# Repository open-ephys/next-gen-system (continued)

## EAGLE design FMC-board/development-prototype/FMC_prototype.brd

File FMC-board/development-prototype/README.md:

# FMC daughter board development prototype

FMC LPC pinout diagram at:
https://docs.google.com/spreadsheets/d/1bgnBP1xqPFtFIQYF-BCybK1KkekfmRYwm2GDAU4D9lo/edit?usp=sharing

Features:

1x FMC connector (use LPC side, seems marginally easier to solder and we dont need the high pin count right now)
https://forums.xilinx.com/t5/Xilinx-Boards-and-Kits/FMC-Where-to-buy/td-p/44218
https://www.samtec.com/standards/fmc#asicdevelopment

~2-4 Omnmetics connectors for intan SPI cables to headstages
Maybe implement 1-2 SPI port with proper electrical decoupling (based on existing headstage decoupling board, but omit DC-DC transformer), but add at least an equal number of non-decoupled ones just in case there's an iissue with the circuit.

Testpoints & SMA connectors for probing things

At least ~4 (protected?) SMA or BNC in- and outputs to/from the FPGA for closed-loop tests.
Do we want to add level shifters or anything that can drive more current than the bare fpga pins?

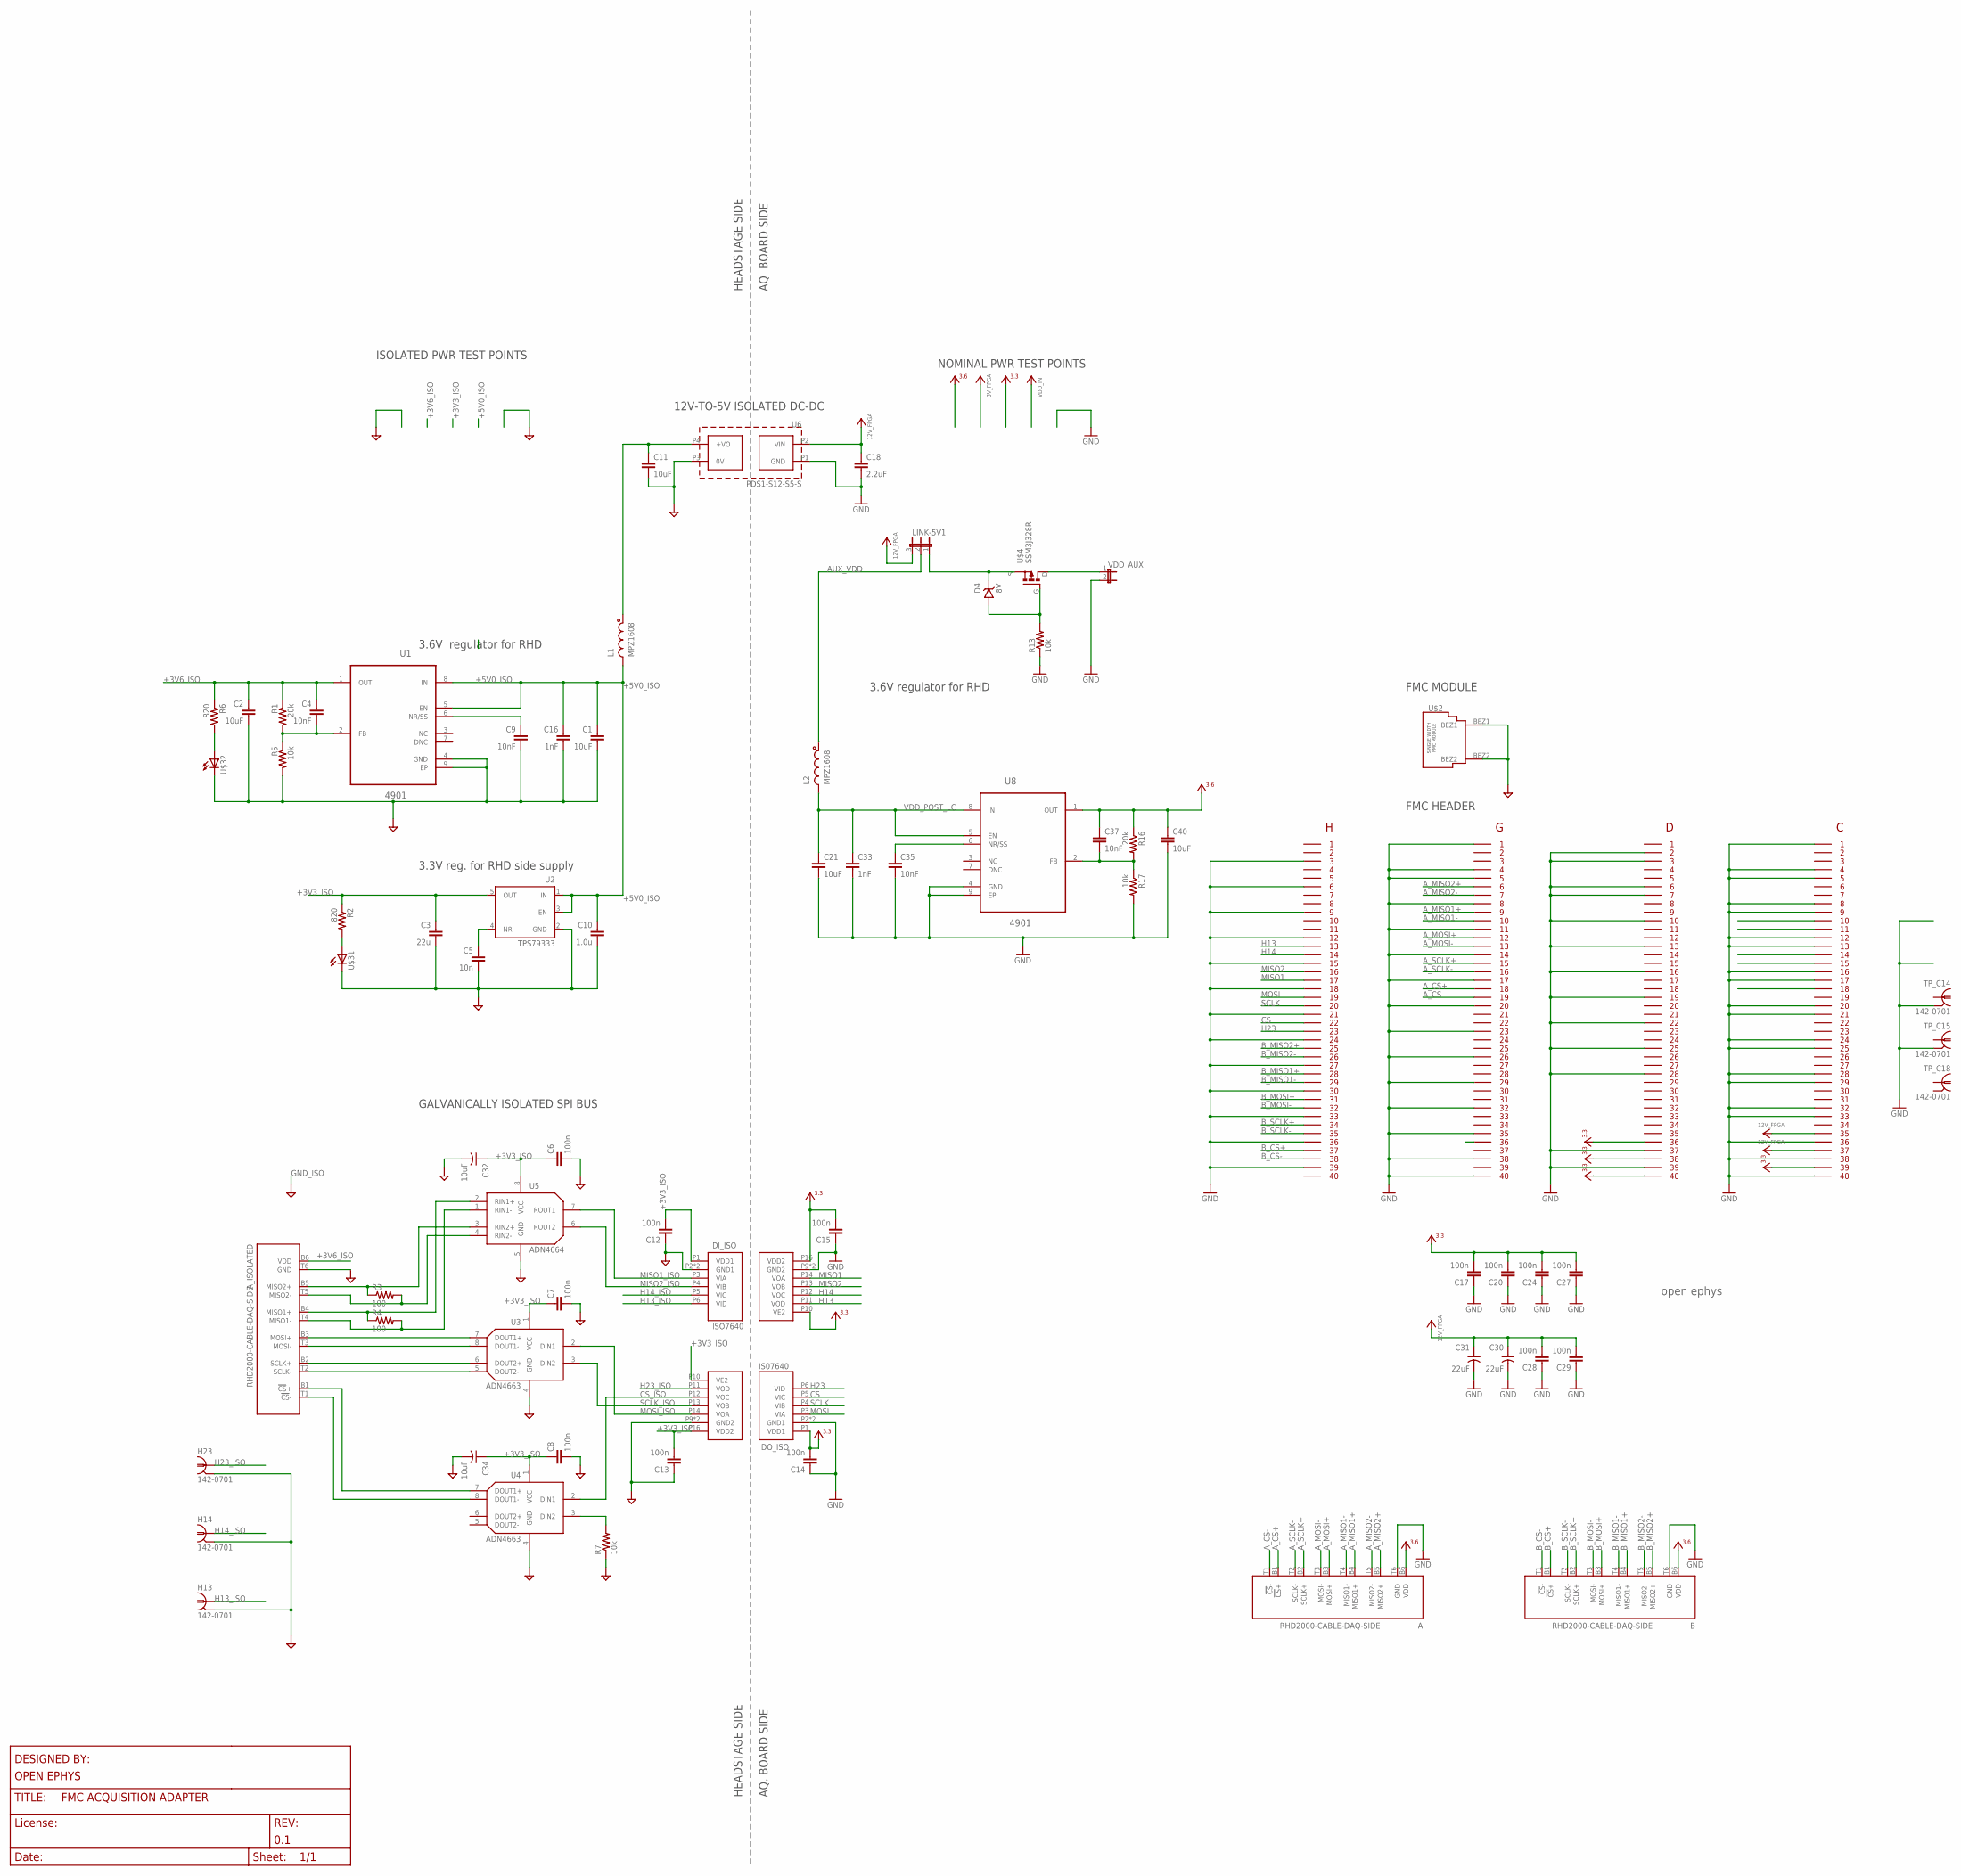
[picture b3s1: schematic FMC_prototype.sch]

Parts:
A: RHD2000-CABLE-DAQ-SIDE; OMNETICS_PZN-12-AA
A_ISOLATED: RHD2000-CABLE-DAQ-SIDE; OMNETICS_PZN-12-AA
B: RHD2000-CABLE-DAQ-SIDE; OMNETICS_PZN-12-AA
C1, C2, C11, C21, C40: 10uF; 1206
C3: 22u; 1206
C4, C9, C35, C37: 10nF; 0603
C5: 10n; 0603
C6, C7, C8, C12, C13, C14, C15, C17, C20, C24, C27, C28, C29: 100n; 0603
C10: 1.0u; 0805
C16, C33: 1nF; 0603
C18: 2.2uF; 1206
C30, C31: 22uF; 1210-POL
C32, C34: 10uF; 1206-POL
D4: 8V; SOD-323
DI_ISO: ISO7640; SOIC_WIDE_16
DO_ISO: IS07640; SOIC_WIDE_16
FMC: FMC_LPC_160_PIN; FMC_LPC_MALE_WITH_SP601_BSILK
H13, H14, H23: 142-0701; SMA_JACK_CONREVSMA002-G
L1, L2: MPZ1608; 0603
LINK-5V1: JP2E; JP2
R1, R16: 20k; 0603
R2, R6: 820; 0603
R3, R4: 100; 0603
R5, R7, R13, R17: 10k; 0603
TP_C14, TP_C15, TP_C18: 142-0701; SMA_JACK_142-0701-201
U1, U8: 4901; SOP65P490X110-9N
U2: TPS79333; SOT-23-5
U3, U4: ADN4663; SOIC127P500X400-8N
U5: ADN4664; SOIC127P500X400-8N
U6: PDS1-S12-S5-S; PDS1
U$1: OPEN_EPHYS_LOGO
U$2: FMC_SINGLE_WIDTH_MODULE
U$3: LED_2X_VERTICAL; 569-011X-X00_LED_ARRAY
U$4: SSM3J328R; SOT23-GSD
VDD_AUX: JP2E_THRU-HOLE; JP2

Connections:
12V_FPGA: C18.1, C28.2, C29.2, C30.+, C31.+, FMC.P$155, FMC.P$157, LINK-5V1.3, U6.P2 (VIN)
+3V3: C14.2, C15.2, C17.2, C20.2, C24.2, C27.2, DI_ISO.P10 (VE2), DI_ISO.P16 (VDD2), DO_ISO.P1 (VDD1), FMC.P$116, FMC.P$118, FMC.P$120, FMC.P$159
+3V3_ISO: C3.1, C6.1, C7.1, C8.1, C12.2, C13.2, C32.+, C34.+, DI_ISO.P1 (VDD1), DO_ISO.P10 (VE2), DO_ISO.P16 (VDD2), R2.1, U2.5 (OUT), U3.1 (VCC), U4.1 (VCC), U5.8 (VCC)
+3V6: A.B6 (VDD), B.B6 (VDD), C37.1, C40.1, R16.1, U8.1 (OUT)
+3V6_ISO: A_ISOLATED.B6 (VDD), C2.1, C4.1, R1.1, R6.1, U1.1 (OUT)
+5V0_ISO: C1.1, C10.1, C16.1, L1.2, U1.5 (EN), U1.8 (IN), U2.1 (IN), U2.3 (EN)
+5V0_ISO-PRE: C11.1, L1.1, U6.P4 (+VO)
AGND1: C37.2, R16.2, R17.1, U8.2 (FB)
AGND2: C4.2, R1.2, R5.1, U1.2 (FB)
AUX_VDD: L2.1, LINK-5V1.2
A_CS+: A.B1 (!CS!+), FMC.P$58
A_CS-: A.T1 (!CS!-), FMC.P$59
A_MISO1+: A.B4 (MISO1+), FMC.P$49
A_MISO1-: A.T4 (MISO1-), FMC.P$50
A_MISO2+: A.B5 (MISO2+), FMC.P$46
A_MISO2-: A.T5 (MISO2-), FMC.P$47
A_MOSI+: A.B3 (MOSI+), FMC.P$52
A_MOSI-: A.T3 (MOSI-), FMC.P$53
A_SCLK+: A.B2 (SCLK+), FMC.P$55
A_SCLK-: A.T2 (SCLK-), FMC.P$56
B_CS+: B.B1 (!CS!+), FMC.P$37
B_CS-: B.T1 (!CS!-), FMC.P$38
B_MISO1+: B.B4 (MISO1+), FMC.P$28
B_MISO1-: B.T4 (MISO1-), FMC.P$29
B_MISO2+: B.B5 (MISO2+), FMC.P$25
B_MISO2-: B.T5 (MISO2-), FMC.P$26
B_MOSI+: B.B3 (MOSI+), FMC.P$31
B_MOSI-: B.T3 (MOSI-), FMC.P$32
B_SCLK+: B.B2 (SCLK+), FMC.P$34
B_SCLK-: B.T2 (SCLK-), FMC.P$35
C10: FMC.P$130
C11: FMC.P$131
C14: FMC.P$134
C18: FMC.P$138
CS: DO_ISO.P5 (VIC), FMC.P$22
CS+_ISOLATED: A_ISOLATED.B1 (!CS!+), U4.7 (DOUT1+)
CS-_ISOLATED: A_ISOLATED.T1 (!CS!-), U4.8 (DOUT1-)
CS_ISO: DO_ISO.P12 (VOC), U4.2 (DIN1)
GND: A.T6 (GND), B.T6 (GND), C14.1, C15.1, C17.1, C18.2, C20.1, C21.2, C24.1, C27.1, C28.1, C29.1, C30.-, C31.-, C33.2, C35.2, C40.2, DI_ISO.P9 (GND2), DI_ISO.P15 (GND2), DO_ISO.P2 (GND1), DO_ISO.P8 (GND1), FMC.GNDA (GND), FMC.GNDB (GND), FMC.P$3, FMC.P$6, FMC.P$9, FMC.P$12, FMC.P$15, FMC.P$18, FMC.P$21, FMC.P$24, FMC.P$27, FMC.P$30, FMC.P$33, FMC.P$36, FMC.P$39, FMC.P$41, FMC.P$44, FMC.P$45, FMC.P$48, FMC.P$51, FMC.P$54, FMC.P$57, FMC.P$60, FMC.P$63, FMC.P$66, FMC.P$69, FMC.P$72, FMC.P$75, FMC.P$78, FMC.P$80, FMC.P$82, FMC.P$83, FMC.P$86, FMC.P$87, FMC.P$90, FMC.P$93, FMC.P$96, FMC.P$99, FMC.P$102, FMC.P$105, FMC.P$108, FMC.P$117, FMC.P$119, FMC.P$121, FMC.P$124, FMC.P$125, FMC.P$128, FMC.P$129, FMC.P$132, FMC.P$133, FMC.P$136, FMC.P$137, FMC.P$140, FMC.P$141, FMC.P$144, FMC.P$145, FMC.P$148, FMC.P$149, FMC.P$152, FMC.P$153, FMC.P$156, FMC.P$158, FMC.P$160, R13.1, R17.2, TP_C14.GND$1 (2), TP_C14.GND$2 (2), TP_C14.GND$3 (2), TP_C14.GND$4 (2), TP_C15.GND$1 (2), TP_C15.GND$2 (2), TP_C15.GND$3 (2), TP_C15.GND$4 (2), U6.P1 (GND), U8.4 (GND), U8.9 (EP), VDD_AUX.2
GND_ISO: A_ISOLATED.T6 (GND), C1.2, C2.2, C3.2, C5.2, C6.2, C7.2, C8.2, C9.2, C10.2, C11.2, C12.1, C13.1, C16.2, C32.-, C34.-, DI_ISO.P2 (GND1), DI_ISO.P8 (GND1), DO_ISO.P9 (GND2), DO_ISO.P15 (GND2), H13.GND$1 (2), H13.GND$2 (2), H13.GND$3 (2), H13.GND$4 (2), H14.GND$1 (2), H14.GND$2 (2), H14.GND$3 (2), H14.GND$4 (2), H23.GND$1 (2), H23.GND$2 (2), H23.GND$3 (2), H23.GND$4 (2), R5.2, R7.1, U1.4 (GND), U1.9 (EP), U2.2 (GND), U3.4 (GND), U4.4 (GND), U5.5 (GND), U6.P3 (0V), U$2.BEZ1, U$2.BEZ2, U$3.C1 (C), U$3.C2 (C)
H13: DI_ISO.P11 (VOD), FMC.P$13
H13_ISO: DI_ISO.P6 (VID), H13.CLK (1)
H14: DI_ISO.P12 (VOC), FMC.P$14
H14_ISO: DI_ISO.P5 (VIC), H14.CLK (1)
H23: DO_ISO.P6 (VID), FMC.P$23
H23_ISO: DO_ISO.P11 (VOD), H23.CLK (1)
MISO1: DI_ISO.P14 (VOA), FMC.P$17
MISO1+_ISOLATED: A_ISOLATED.B4 (MISO1+), R4.1, U5.2 (RIN1+)
MISO1-_ISOLATED: A_ISOLATED.T4 (MISO1-), R4.2, U5.1 (RIN1-)
MISO1_ISO: DI_ISO.P3 (VIA), U5.7 (ROUT1)
MISO2: DI_ISO.P13 (VOB), FMC.P$16
MISO2+_ISOLATED: A_ISOLATED.B5 (MISO2+), R3.1, U5.3 (RIN2+)
MISO2-_ISOLATED: A_ISOLATED.T5 (MISO2-), R3.2, U5.4 (RIN2-)
MISO2_ISO: DI_ISO.P4 (VIB), U5.6 (ROUT2)
MOSI: DO_ISO.P3 (VIA), FMC.P$19
MOSI_ISO: DO_ISO.P14 (VOA), U3.2 (DIN1)
unnamed: C35.1, U8.6 (NR/SS)
unnamed: D4.C, LINK-5V1.1, U$4.S
unnamed: C9.1, U1.6 (NR/SS)
unnamed: R7.2, U4.3 (DIN2)
unnamed: D4.A, R13.2, U$4.G
unnamed: U$4.D, VDD_AUX.1
unnamed: R6.2, U$3.A2 (A)
unnamed: R2.2, U$3.A1 (A)
unnamed: A_ISOLATED.B3 (MOSI+), U3.7 (DOUT1+)
unnamed: A_ISOLATED.T3 (MOSI-), U3.8 (DOUT1-)
unnamed: A_ISOLATED.B2 (SCLK+), U3.6 (DOUT2+)
unnamed: A_ISOLATED.T2 (SCLK-), U3.5 (DOUT2-)
unnamed: C5.1, U2.4 (NR)
SCLK: DO_ISO.P4 (VIB), FMC.P$20
SCLK_ISO: DO_ISO.P13 (VOB), U3.3 (DIN2)
TP7: FMC.P$135
VDD_POST_LC: C21.1, C33.1, L2.2, U8.5 (EN), U8.8 (IN)

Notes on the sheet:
HEADSTAGE SIDE
AQ. BOARD SIDE
3.3V reg. for RHD side supply
3.6V regulator for RHD
12V-TO-5V ISOLATED DC-DC
ISOLATED PWR TEST POINTS
NOMINAL PWR TEST POINTS
3.6V regulator for RHD
GALVANICALLY ISOLATED SPI BUS
FMC HEADER
FMC MODULE

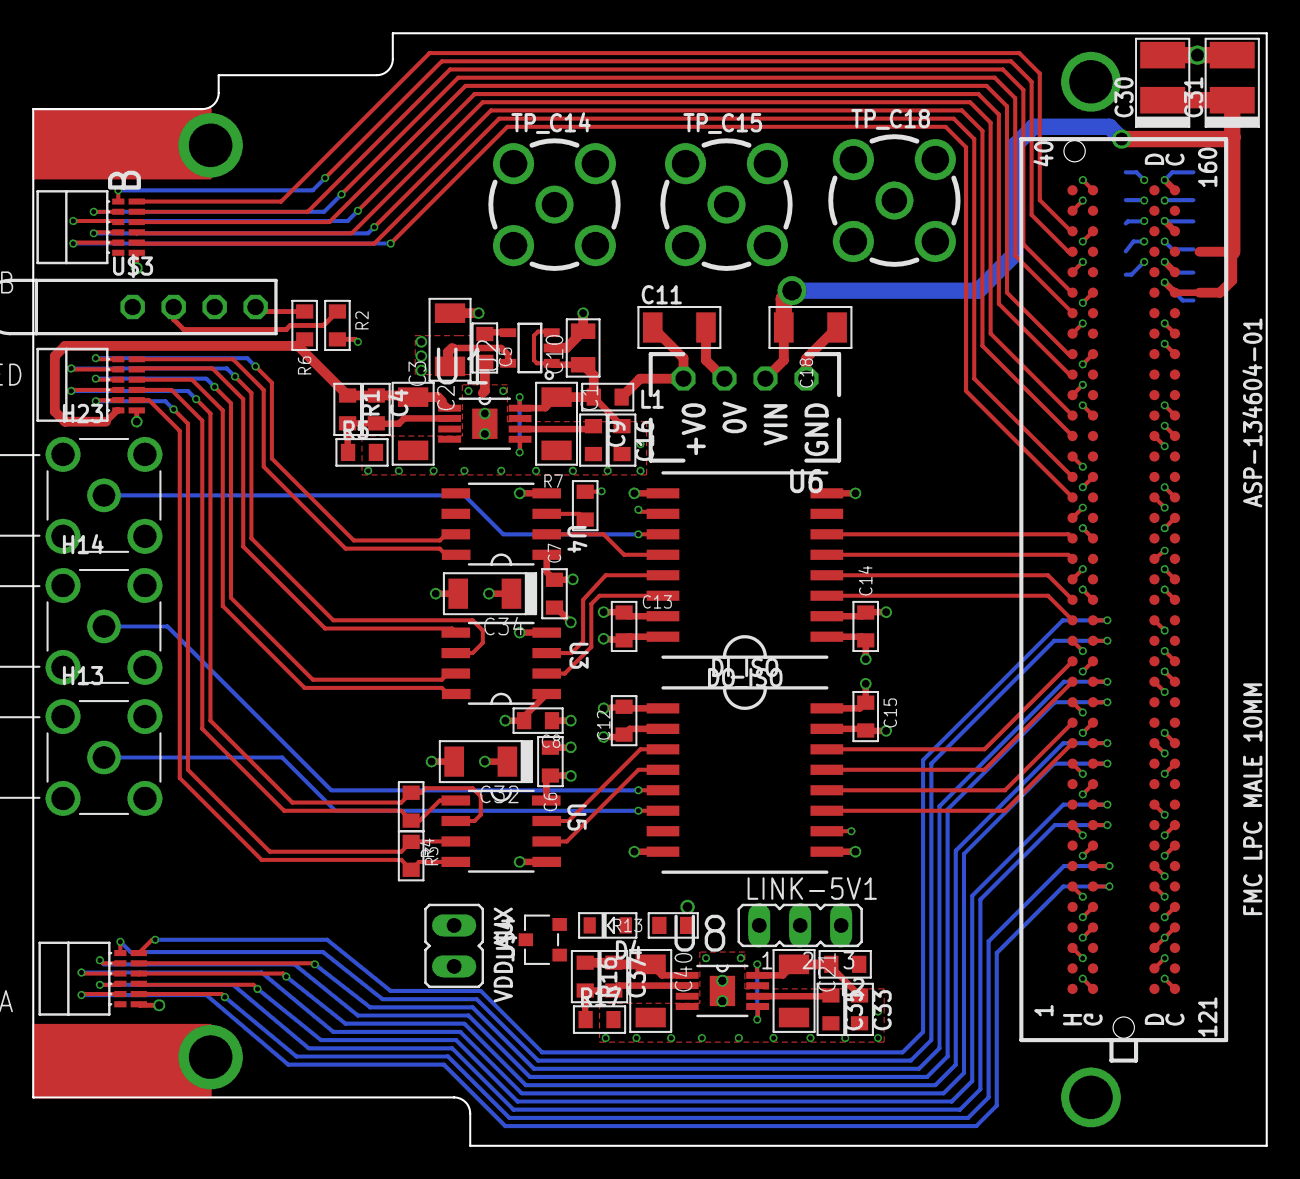
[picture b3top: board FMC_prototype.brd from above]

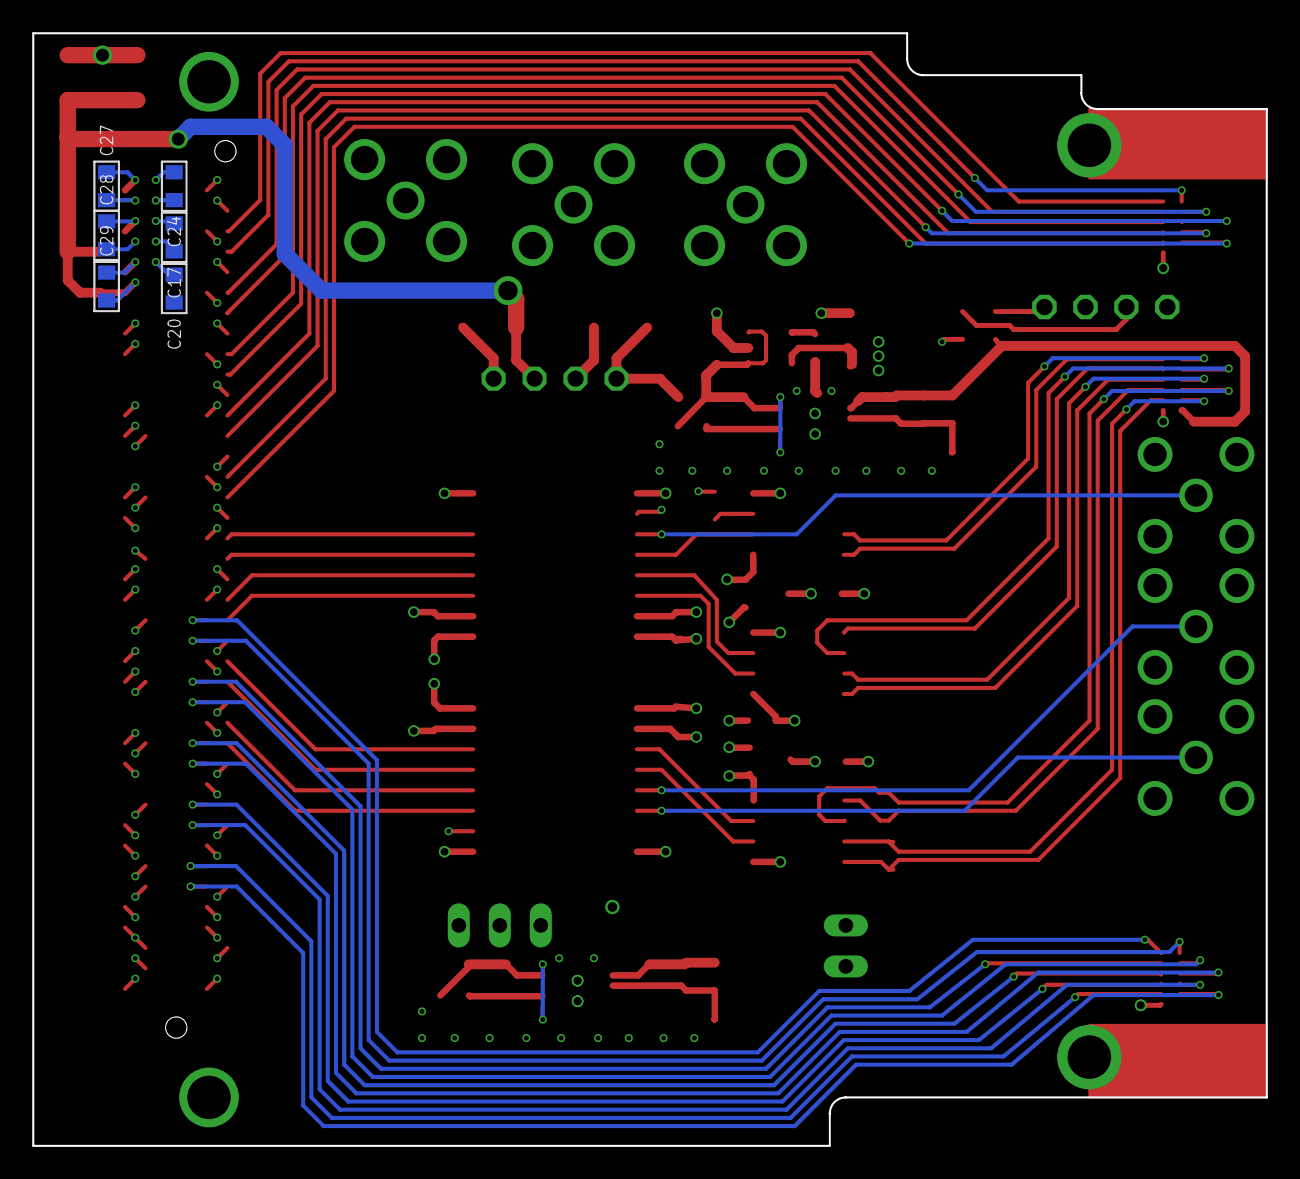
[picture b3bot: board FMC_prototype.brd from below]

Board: 4 copper layers, 76.5 x 69.0 mm, 71 parts (7 on the bottom side), 68 nets.

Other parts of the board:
U$16: INTAN_LOGO

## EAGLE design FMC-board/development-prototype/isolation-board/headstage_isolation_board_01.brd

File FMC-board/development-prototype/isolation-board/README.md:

# headstage-isolation-board
isolation board for RHD headstge, electrically decouples headstage from aq. board.
This could be useful for mitigating recording noise in some scenarious, or simplify proper grounding practive, especially if multiple recording rigs share the same acquisition board. Eventually, this device could be used to provide safety for human EEG or intracortical applications, but this would require extensive testing and approval procedures.

*This device has not been tested and is not considered safe for any use case. Only use this if you are approved to do so independently.*

# operating principle
This isolation board translates the LVDS signals to a single ended CMOS signal, isolates this signal and translates it back to LVDS. Power isolation is accomplished through a separate 5V isolation transformer.

Based on Analog Devices ADUM3440 isolators 9 http://www.analog.com/media/en/technical-documentation/data-sheets/ADuM3440_3441_3442.pdf )
UL recognition: 2500 V rms for 1 minute per UL 1577,  CSA Component Acceptance Notice #5A, VDE certificate of conformity, DIN V VDE V 0884-10 (VDE V 0884-10):2006-12 
V_IORM = 560 V peak

LVDS<-> CMOS trsnalation is done via on Analog Devices ADN4664 Dual, 3 V, CMOS, LVDS Differential Line Receivers ( http://www.analog.com/media/en/technical-documentation/data-sheets/ADN4664.pdf ) and ADN4663 Dual, 3 V, CMOS, LVDS High Speed Differential Drivers ( http://www.analog.com/media/en/technical-documentation/data-sheets/ADN4663.pdf )

Power isolation is done with a Murata NMV0505 3kVDC Isolated 5V DC/DC Converters ( http://power.murata.com/data/power/ncl/kdc_nmv.pdf )

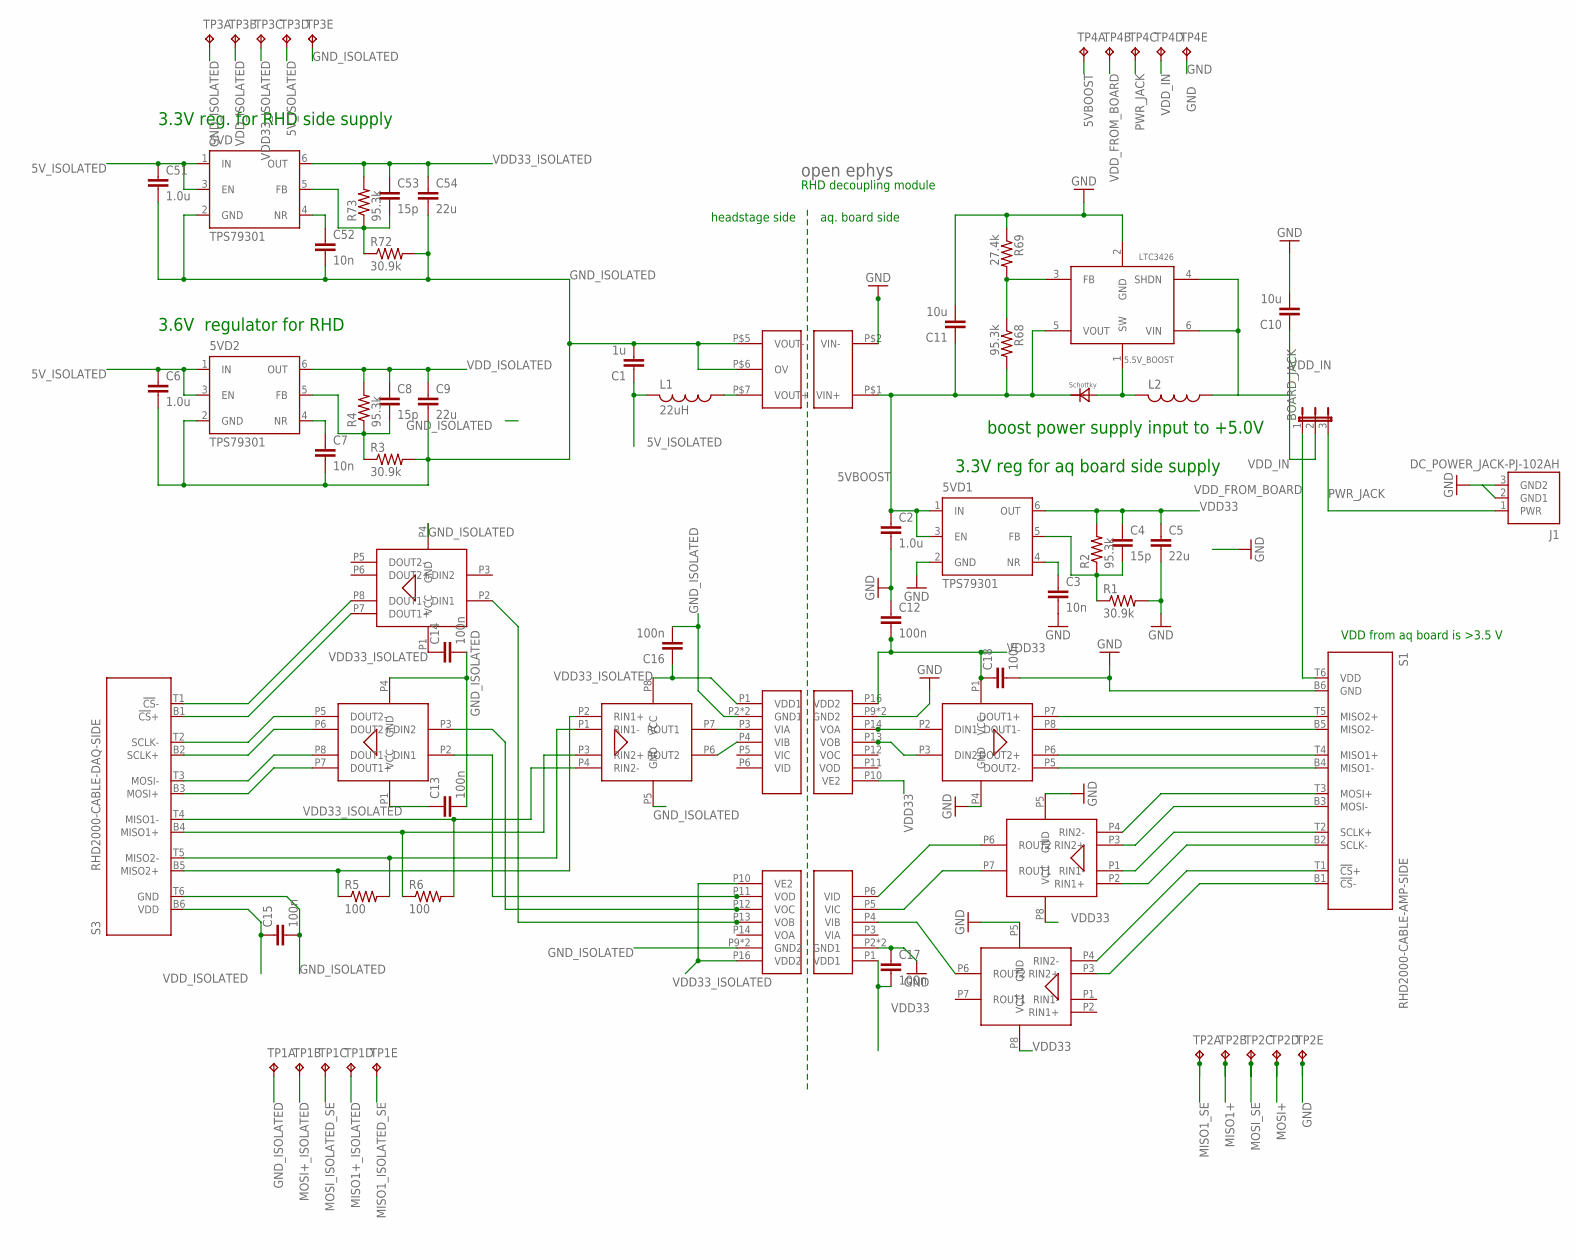
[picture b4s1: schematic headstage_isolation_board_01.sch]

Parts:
5.5V_BOOST: LTC3426; SOT23-6
5VD, 5VD1, 5VD2: TPS79301; SOT-23-6
BOARD_JACK: JP2E; JP2
C1: 1u; 1206
C2, C6, C51: 1.0u; 0805
C3, C7, C52: 10n; 0603
C4, C8, C53: 15p; 0603
C5, C9, C54: 22u; 1206
C10, C11: 10u; 1206
C12, C13, C14, C15, C16, C17, C18: 100n; 0603
D1: MBRA210LT3-D
J1: DC_POWER_JACK-PJ-102AH; PJ-102AH
L1: 22uH; 1206
L2: L_1206; 1206
R1, R3, R72: 30.9k; 0603
R2, R4, R68, R73: 95.3k; 0603
R5, R6: 100; 0603
R69: 27.4k; 0603
S1: RHD2000-CABLE-AMP-SIDE; OMNETICS_PZN-12-AA
S3: RHD2000-CABLE-DAQ-SIDE; OMNETICS_PZN-12-AA
TP1, TP2, TP3, TP4: TP5P5-25-13; P5-25-13
U$1: OPEN_EPHYS_LOGO
U$2, U$10: ADUM3440; SOIC_WIDE_16
U$4, U$5, U$9: ADN4663; 8-SOIC
U$6, U$7, U$8: ADN4664; 8-SOIC
U$12: NMV0505

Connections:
5VBOOST: 5.5V_BOOST.5 (VOUT), 5VD1.1 (IN), 5VD1.3 (EN), C2.1, C11.1, D1.NEG, R68.2, TP4.TP-1, U$12.P$1 (VIN+)
5V_ISOLATED: 5VD.1 (IN), 5VD.3 (EN), 5VD2.1 (IN), 5VD2.3 (EN), C1.1, C6.1, C51.1, L1.2, TP3.TP-4
CS+: S1.T1 (!CS!+), U$8.P4 (RIN2-)
CS+_ISOLATED: S3.B1 (!CS!+), U$9.P7 (DOUT1+)
CS-: S1.B1 (!CS!-), U$8.P3 (RIN2+)
CS-_ISOLATED: S3.T1 (!CS!-), U$9.P8 (DOUT1-)
CS_ISOLATED_SE: U$2.P13 (VOB), U$9.P2 (DIN1)
CS_SE: U$2.P4 (VIB), U$8.P6 (ROUT2)
GND: 5.5V_BOOST.2 (GND), 5VD1.2 (GND), C2.2, C3.2, C5.2, C10.2, C11.2, C12.1, C17.1, C18.2, J1.2 (GND1), J1.3 (GND2), R1.2, R69.1, S1.B6 (GND), TP2.TP-5, TP4.TP-5, U$2.P2 (GND1), U$2.P8 (GND1), U$4.P4 (GND), U$7.P5 (GND), U$8.P5 (GND), U$10.P9 (GND2), U$10.P15 (GND2), U$12.P$2 (VIN-)
GND4: C15.2
GND_ISOLATED: 5VD.2 (GND), 5VD2.2 (GND), C1.2, C6.2, C7.2, C9.2, C13.2, C14.2, C16.2, C51.2, C52.2, C54.2, R3.2, R72.2, S3.T6 (GND), TP1.TP-1, TP3.TP-1, TP3.TP-5, U$2.P9 (GND2), U$2.P15 (GND2), U$5.P4 (GND), U$6.P5 (GND), U$9.P4 (GND), U$10.P2 (GND1), U$10.P8 (GND1), U$12.P$5 (VOUT-), U$12.P$6 (OV)
MISO1+: S1.T4 (MISO1+), TP2.TP-2, U$4.P6 (DOUT2+)
MISO1+_ISOLATED: R6.1, S3.B4 (MISO1+), TP1.TP-4, U$6.P3 (RIN2+)
MISO1-: S1.B4 (MISO1-), U$4.P5 (DOUT2-)
MISO1-_ISOLATED: R6.2, S3.T4 (MISO1-), U$6.P4 (RIN2-)
MISO1_ISOLATED_SE: TP1.TP-5, U$6.P6 (ROUT2), U$10.P4 (VIB)
MISO1_SE: TP2.TP-1, U$4.P3 (DIN2), U$10.P13 (VOB)
MISO2+: S1.T5 (MISO2+), U$4.P7 (DOUT1+)
MISO2+_ISOLATED: R5.1, S3.B5 (MISO2+), U$6.P2 (RIN1+)
MISO2-: S1.B5 (MISO2-), U$4.P8 (DOUT1-)
MISO2-_ISOLATED: R5.2, S3.T5 (MISO2-), U$6.P1 (RIN1-)
MISO2_ISOLATED_SE: U$6.P7 (ROUT1), U$10.P3 (VIA)
MISO2_SE: U$4.P2 (DIN1), U$10.P14 (VOA)
MOSI+: S1.T3 (MOSI+), TP2.TP-4, U$7.P4 (RIN2-)
MOSI+_ISOLATED: S3.B3 (MOSI+), TP1.TP-2, U$5.P7 (DOUT1+)
MOSI-: S1.B3 (MOSI-), U$7.P3 (RIN2+)
MOSI-_ISOLATED: S3.T3 (MOSI-), U$5.P8 (DOUT1-)
MOSI_ISOLATED_SE: TP1.TP-3, U$2.P11 (VOD), U$5.P2 (DIN1)
MOSI_SE: TP2.TP-3, U$2.P6 (VID), U$7.P6 (ROUT2)
unnamed: L1.1, U$12.P$7 (VOUT+)
unnamed: 5VD1.4 (NR), C3.1
unnamed: 5VD1.5 (FB), C4.2, R1.1, R2.1
unnamed: 5VD2.4 (NR), C7.1
unnamed: 5VD2.5 (FB), C8.2, R3.1, R4.1
unnamed: 5VD.4 (NR), C52.1
unnamed: 5VD.5 (FB), C53.2, R72.1, R73.1
unnamed: 5.5V_BOOST.3 (FB), R68.1, R69.2
unnamed: 5.5V_BOOST.1 (SW), D1.POS, L2.2
PWR_JACK: BOARD_JACK.3, J1.1 (PWR), TP4.TP-3
SCLK+: S1.T2 (SCLK+), U$7.P1 (RIN1-)
SCLK+_ISOLATED: S3.B2 (SCLK+), U$5.P6 (DOUT2+)
SCLK-: S1.B2 (SCLK-), U$7.P2 (RIN1+)
SCLK-_ISOLATED: S3.T2 (SCLK-), U$5.P5 (DOUT2-)
SCLK_ISOLATED_SE: U$2.P12 (VOC), U$5.P3 (DIN2)
SCLK_SE: U$2.P5 (VIC), U$7.P7 (ROUT1)
VDD33: 5VD1.6 (OUT), C4.1, C5.1, C12.2, C17.2, C18.1, R2.2, U$2.P1 (VDD1), U$4.P1 (VCC), U$7.P8 (VCC), U$8.P8 (VCC), U$10.P10 (VE2), U$10.P16 (VDD2)
VDD33_ISOLATED: 5VD.6 (OUT), C13.1, C14.1, C16.1, C53.1, C54.1, R73.2, TP3.TP-3, U$2.P10 (VE2), U$2.P16 (VDD2), U$5.P1 (VCC), U$6.P8 (VCC), U$9.P1 (VCC), U$10.P1 (VDD1)
VDD_FROM_BOARD: BOARD_JACK.1, S1.T6 (VDD), TP4.TP-2
VDD_IN: 5.5V_BOOST.4 (SHDN), 5.5V_BOOST.6 (VIN), BOARD_JACK.2, C10.1, L2.1, TP4.TP-4
VDD_ISOLATED: 5VD2.6 (OUT), C8.1, C9.1, C15.1, R4.2, S3.B6 (VDD), TP3.TP-2

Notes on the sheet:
headstage side
aq. board side
VDD from aq board is >3.5 V
RHD decoupling module
boost power supply input to +5.0V
3.3V reg. for RHD side supply
3.3V reg for aq board side supply
3.6V regulator for RHD

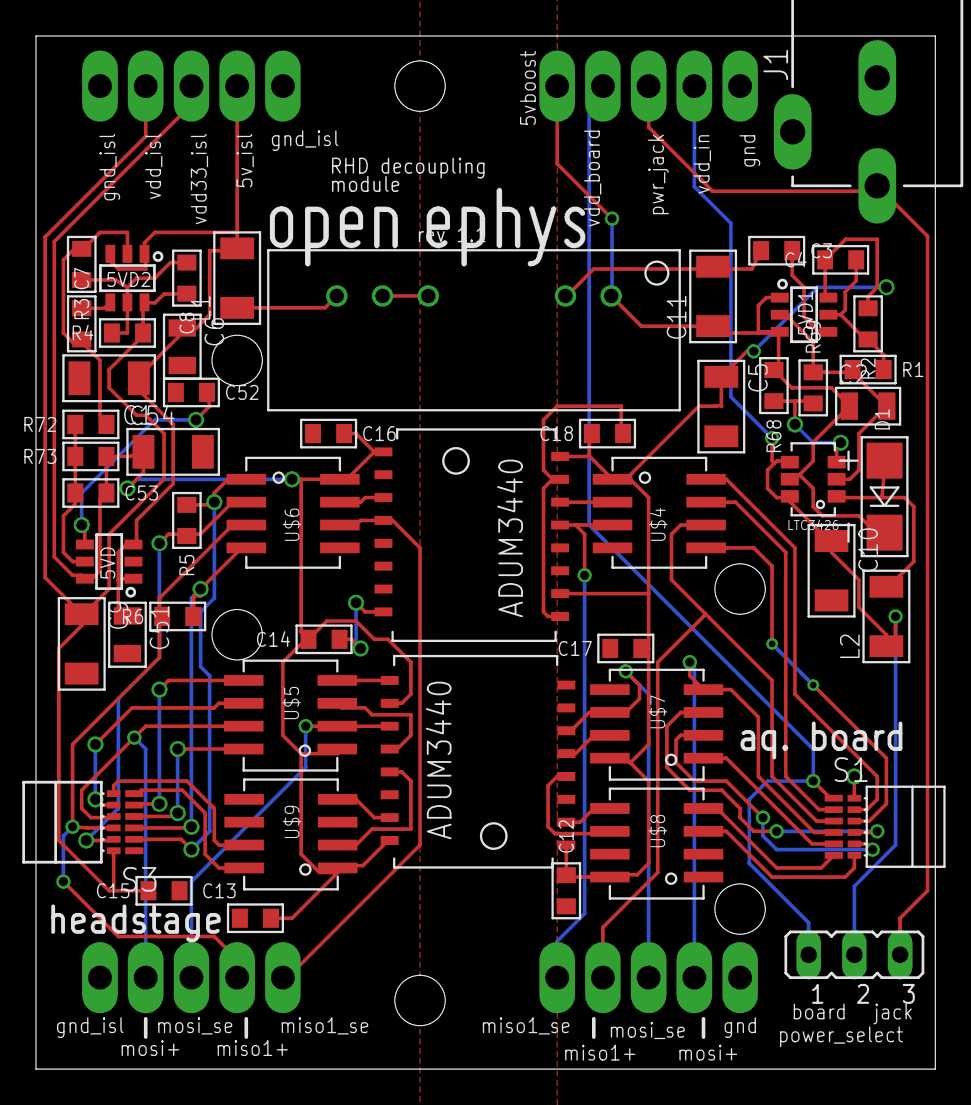
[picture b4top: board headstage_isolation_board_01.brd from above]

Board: 2 copper layers, 50.0 x 57.4 mm, 57 parts (0 on the bottom side), 49 nets.

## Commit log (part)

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2016-02-25 init readme
2016-02-25 initial commit of folder structure
2016-02-25 added copy of isolation board
    might be useful to work from, or see if there's already a verified design for this
2016-02-25 more folders
2016-02-25 adde readme
2016-02-26 Initial commit FMC board prototype
    this is pretty much just a wiped version of the board from
    http://www.ohwr.org/projects/lpcfmc12pexp/files
    Still need to verify everything on this, then figure out the
    dimensions, pinout etc. and then start adding in things
2016-02-28 initial board layout fpga side
2016-02-28 added basic isolator circuitry sch
2016-02-28 initial layout isolated section
2016-02-28 added LPC pinout ref
2016-02-28 more power layout
    started adding pins on the LPC FMC connector
2016-02-29 added 3.6V regulator for non-isolated SPI connectors
2016-02-29 cleanup&labels
2016-02-29 started adding SPI signals for A
    still not routed
2016-02-29 connected B SPI
2016-02-29 routed B SPI connector
2016-02-29 small cleanups
2016-03-01 more small cleanups
2016-03-04 added link to google spreadsheet with pinout
2016-03-04 added reference for kintex 7 eval board
    from http://www.xilinx.com/products/boards-and-kits/ek-k7-kc705-g.html#documentation
2016-03-04 added proper ground plane
    this is now 4 layers but its somewhat cleaner this way
2016-03-04 added testpoints
    still some unrouted parts
2016-03-04 routed isolated testpoints
    likely still errors in there
2016-03-05 cleanup, starting DRC
2016-03-05 clearing all but layer setup and silkscreen overlap warnings
2016-03-05 added spreadsheet of pinout diagram
    same as https://docs.google.com/spreadsheets/d/1bgnBP1xqPFtFIQYF-BCybK1KkekfmRYwm2GDAU4D9lo/edit?usp=sharing
2016-03-06 added optional DC DC converter
    12V > 5V DC DC for powering headstage etc. can still be bypassed with jumper
2016-03-07 More or less done checking power section of schematic.
2016-03-07 Started working on digital ports.
2016-03-07 Cleaning up schematic as a means to understand and verify it.
2016-03-07 Looks like isolated 5V was wired to output of isolated 3.6V regulator and input is floating to both isolated regulators. In the middle of fixing that.
2016-03-07 More digital port cleanup.
2016-03-08 Fixed reversed polarity on LVDS drvr/recv's.
2016-03-08 Almost ready to merge with master. Needs a couple more ERC checks.
2016-03-08 Finished updating the schematic
    - TODOs moved to the FMC board's README.md rather than the top level
    one.
    - Need to verify that the dev board supports internal LVDS termination
2016-03-08 A bit of organization.
2016-03-08 rough layout
2016-03-08 more layout
2016-03-09 layout mostly cleaned up now
    still needs proper DRC, probably ERC and almost all labels etc need to
    be fixed
2016-03-09 small layout fixes
2016-03-09 improved B headstage routing
    no more branches going to test points
2016-03-12 added labels to testpoints
2016-03-12 Reworking power planes and differential signal routing
    - Removed top/bottom ground planes.
    - High speed signal ended signals: return current flows beneath trace
    - Differential signals: avoid large loop areas. Ideally, trances should
    be parallel until they terminate on a pad or through characteristic
    impedance.
    - The large test points are problematic. I really think we should
2016-03-12 Changes to differential pair layout and power
    - Mostly finished with non-isolated side.
    - Moved decoupling caps closer to target ICs and provided low impedance
    paths to ground power
    - Differential traces wired together
    - Got rid of non-isolated side 3.3V regulator because there is just no
    reason non to use the FMC 3.3V rail -- if that does not work, then the
2016-03-13 Added copy of vita-57.1 standard.
2016-03-13 Toward VITA-57.1 compliance
    - Found pad alignment issues in the SOIC16 digital isolation chips.
    Fixed that.
    - Layout changes informed by VITA 57.1 and several FMC modules designed
    by CERN for data collection in high-energy physics experiments.
    - Removed power jacks for now. Replaced with simple headers and reverse
    polarity protection to make up for the automatic polarity protection
2016-03-13 About 50% through routing
    - The FMC<->Driver/Reciver<->Isolator<->Driver/Receiver path needs to be
    rearranged to minimize crossovers
2016-03-14 Removed FPGA side LVDS drivers/receivers
    - Not needed as all FMC connections can be configured as single
    ended
    - Started BOM
    - Switched to RA SMAs on the panel side of board
2016-03-14 Lots of routing simplification
    - Moved non-isolated SPI buses onto there own IO on the FMC connector
    since there is plenty of that. Got rid of the branches and jumper
    resistors as a result.
    - Only a bit more wiring todo before be ERC/DRC stage.
2016-03-14 More routing.
2016-03-15 Hard routing complete
    - Inner SMAs need hookups
    - Should bezel be tied to GND_ISO?
    - Re-add testpoints (pad style)
    - Silkscreen...
2016-03-15 Done with initial routing of FMC-compliant board
    - Get others to examine before messing with silkscreen a putting in test
    points.
2016-03-15 Cleanup. Added images of schematic/board.
2016-03-16 tightened routing a bit & added 3v3 test point
2016-03-16 added schottky diodes for FPGA input protection
2016-03-16 cleaning up diode layout
2016-03-16 some labelling
2016-03-16 Overvoltage protection and silkscreen cleanup
    - Finished adding Schottky protection rectifiers to all SMA inputs,
    included isolated lines.
    - Left the Bezel connector floating, since this is supposed to be
    galvanically isolated from the FPGA ground. Eventually, we will
    probably tie to GND_ISO, but its more trouble than its worth now
    - Cleaned up silkscreen
2016-03-17 More silkscreen fixes and test points
    - Added test pads for digital lines on paths through isolation
    circuitry. Used small inline padsto prevent stubs.
    - Silkscreen looks pretty good now.
    - Boards needs a fresh look over then fab, I think.
2016-03-17 Added ferrite chip datasheet.
2016-03-17 Final, minor changes to sinkscreen and tp's
    - Added isolated power test points
    - Moved Jakobs annotations to the tplace and bplace layers, so that they
    will be included in the silkscreen using the CAM job I added
    - Added a well-tested CAM job for 4-layer boards
    - Added resultant gerber files for PCB and stencil
2016-03-17 Made single ended spi signal traces thicker
    set them to 0.015" instead of 0.01" to match 50 Ohm impedance a bit more closely:
    see http://www.eeweb.com/toolbox/microstrip-impedance
    assuming 1oz copper, 0.25mm height (for ~1.2mm total), ER=4.5, and width 0.015" gets 54Ohm
2016-03-18 small cleanups on 50ohm line and silkscreen
2016-03-18 Rerouted MISOB so it does not use _CC lines
    - CC means clock capable lines and are intented for a different standard
    than LVDS. They should be fine for LVDS signaling, but we had plenty
    of normal LVDS so better safe than sorry
2016-03-18 Fixed SMA component names to match new FMC loctaions.
2016-03-22 Final changes to layout before fabrication
    - Gerbers are being sent to Seeed for fabrication
    - I will tag this Rev 0.1
2016-04-06 updated pinout link
2016-04-06 added link to wiki
2016-04-13 samtec docs say simple reflow without holding down the sodlercharge pins should work
2016-04-13 typo
2016-04-17 Added hardware license info to README.md
2016-04-20 Started TODO list for Rev. 1.0 of the FMC module.
2016-04-22 initial commit folders and gitignore etc for hardware test firmware
2016-04-22 added gitignore
2016-04-22 Complete test project for basic FMC board bring up
    - Contains constraint files
    - Contains some non optimal xillybus IP
    - Contains a .tcl script (build-project.tcl) for
    re-creating project in vivado. Not sure if its
    going to work.
2016-04-23 Started revision 1.0 the PCI form-factor IO module
    - Testing out mechanical and electrical design for intan/digital IO
    module that fits in a standard PCI add-in card slot and connects to
    KC705 via flex FMC cable.
2016-04-23 Added some part selections for the pci-dio board.
2016-04-24 Designed protection network for dio-pci card
    - TTL, LVTTL, CMOS logic level compatible
    - Resistant to incorrect logic levels and low impedance DC or AC sources
2016-04-25 Add new example for project version control
2016-04-26 adding simple constraint file and some test signals alsotrying to add the xci files, lets see if these work on newer vivao versions now
2016-04-26 Added some design ideas to dio-pci README.
2016-04-28 Add pcie-rhythm prototype project
2016-04-28 Add clock generator files
2016-04-28 added fifo xci
2016-04-29 Add config registers and clock configuration
2016-05-01 Acquisition running on isolated port C
2016-05-02 added ram bank xci from older vivado version
2016-05-03 Add flash build constrain
2016-05-08 next gen system HW sketch initial commit
2016-05-08 next-gem-system latencies illustration initial commit
2016-05-08 updated latencies figure
2016-05-08 added latencies png
2016-05-08 added linear overview, small color fixes
2016-05-08 added latency histogram measurements
    from open ephys usb system,
    pcie prototype, and RTXI
2016-05-09 updated HW architecture sketch
2016-05-11 fix file format error
2016-05-11 added illustration of standardized vs. user defined components
2016-05-12 small main sketch fixes
2016-05-12 added FPGA interface illustration
2016-05-17 Fix bad configuration on RAM bank IP file
2016-05-17 Add prebuilt bitfile for the pice firmware
2016-05-28 Intial open instruments low level API specification
    - This was the result of a brainstorming session at the TENSS in Romania
    and provides a skeleton interface specification for the next geb
    system
2016-05-29 Initial commit open instruments whitepaper
2016-05-29 fixed image url
2016-05-29 initial commit proposal slides
    presentation given at SWC on May 25, 2016
    this is not fully up to date yet, but provides a decent introduction to the general idea of the standard
2016-05-29 Added reflection part of API spec, types, argument defs, etc
2016-05-30 some edits
2016-05-30 minor edits
2016-05-31 Add aux input line
2016-06-01 initial commit extended whitepaper
    pretty much just the outline
2016-06-01 extended whitepaper, added latencies and edits
2016-06-01 expanded vhdci spec description
2016-06-01 expanded whitetpaper description of hw, ip cores and api
2016-06-01 fixed whitepaper caption
2016-06-01 added next steps section to extended whitepaper
2016-06-01 more whitepaper edits
2016-06-01 added system sketch to whitepaper
2016-06-01 added curly braces etc to overview
    .. in gimp. There should be a trophy for this maybe?
2016-06-01 typos
2016-06-01 Editable API spec moved to README_EDITABLE.md
    - Generated README.*'s are produced by pandoc. Don't edit these
    directly!
    - Also, some minor fixes.
2016-06-01 Small pandoc fix.
2016-06-01 Some updtes the extended whitepaper.
2016-06-02 edits
2016-06-05 initial commit full spec
    mostly copy pated and extended from the whitepaper
2016-06-05 edits and fixes
2016-06-05 expanded specification
2016-06-06 expanded spec and typos
2016-06-06 expanded spec
2016-06-06 added oiGetNumCOres and oiGetCOreType to API
    just rough outline - signatures likely still wrong
2016-06-06 added 2do: missing port number arg
    on oiGetDeviceType and oiGetCoreType
2016-06-06 expanded API description a bit
    also, typos
2016-06-09 expanded IP core interface spec
2016-06-09 renamed file
2016-06-22 small clarifications and typos
2016-08-04 made RTXI specific HW sketch
2016-11-17 initial commit of spacing test for FMC card for 8 intan SPI connectors
    looks a whole lot like the isolators won;t fit - may have to switch to a smaller package on these and accept a lower isolation standard
2016-11-17 added some cmos/lvds bridge components to check spacing
2016-11-18 added sfn 2016 poster
